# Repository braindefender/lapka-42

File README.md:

[English version of this README](./README_EN.md)

# Лапка 42

Беспроводная эргономичная сплит-клавитура для тех, у кого лапки (:

**Информация:**

|                         |                                 |
| :---------------------- | :------------------------------ |
| **Количество клавиш**   | 42                              |
| **Тип матрицы**         | Диодная                         |
| **Направление диодов**  | Col2Row                         |
| **Совместимые MCU**     | nRF52840 (SuperMini, nice!nano) |
| **Совместимые АКБ**     | 401230                          |
| **Совместимые свитчи**  | Choc v1/v2                      |
| **Свитч-спейсинг**      | Choc (18×17mm)                  |
| **Расположение клавиш** | Splay                           |

**Структура репозитория:**

| Директория | Описание                                              |
| ---------: | :---------------------------------------------------- |
|        3MF | Проект OrcaSlicer (для примера параметров печати)     |
|     Assets | Изображения и фото                                    |
|      Build | Описание [процесса сборки](./Build/BUILD_GUIDE_RU.md) |
|     Fusion | Проект Autodesk Fusion 360                            |
|    Gerbers | Gerber-файлы для производства плат                    |
|      KiCad | Проект KiCad (схема, плата, компоненты)               |
|        STL | 3D-модели частей корпуса                              |

**Части корпуса:**
|   Файл | Описание                                                      |
| -----: | :------------------------------------------------------------ |
| Bottom | Нижняя часть корпуса, имеет вырезы под hotswap-сокеты и диоды |
|  Cover | Крышка для АКБ и кнопки Reset                                 |
|  Frame | Верхняя часть корпуса, для тайп-кластера                      |
|  Thumb | Верхняя часть корпуса, для тамб-кластера                      |

**Разметка пинов:**

> C — колонки, R — строки, нумерация слева направо, сверху вниз

|  Пин  | Левая | Правая |
| :---: | :---: | :----: |
|  C0   |  D4   |  D10   |
|  C1   |  D5   |  D16   |
|  C2   |  D6   |  D14   |
|  C3   |  D7   |  D15   |
|  C4   |  D8   |  D18   |
|  C5   |  D9   |  D19   |
|       |       |
|  R0   |  D2   |  D21   |
|  R1   |  D3   |  D20   |
|  R2   |  D16  |   D8   |
|  R3   |  D10  |   D9   |

## Прошивка

- [`ZMK × Wellum`](https://github.com/braindefender/lapka-zmk-config/tree/lapka-42)
- `RMK × Wellum` — *в разработке*

## История изменений

### v1
- Первичный релиз.

## Фото

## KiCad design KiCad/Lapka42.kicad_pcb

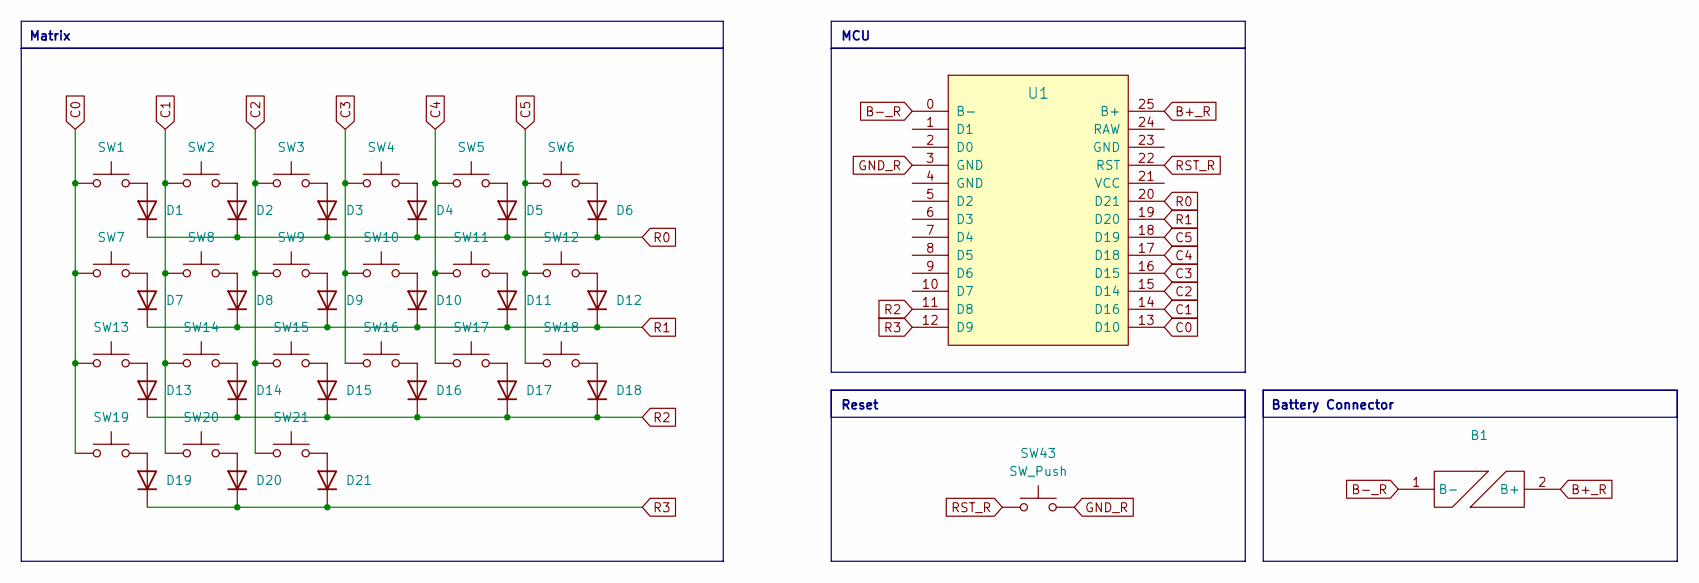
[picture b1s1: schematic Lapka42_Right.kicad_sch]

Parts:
B1: BAT_RECT
D1, D2, D3, D4, D5, D6, D7, D8, D9, D10, D11, D12, D13, D14, D15, D16, D17, D18, D19, D20, D21: D_SOD-323_Increased
SW1, SW2, SW3, SW4, SW5, SW6, SW7, SW8, SW9, SW10, SW11, SW12, SW13, SW14, SW15, SW16, SW17, SW18, SW19, SW20, SW21: SW_Choc_V1V2_HS
SW43: SW_Push; SW_SMD_5x5
U1: U_ProMicro_nRF52840_MidMount

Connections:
B+_R: B1.2 (B+), U1.25 (B+)
B-_R: B1.1 (B-), U1.0 (B-)
C0: SW1.1, SW7.1, SW13.1, SW19.1, U1.13 (D10)
C1: SW2.1, SW8.1, SW14.1, SW20.1, U1.14 (D16)
C2: SW3.1, SW9.1, SW15.1, SW21.1, U1.15 (D14)
C3: SW4.1, SW10.1, SW16.1, U1.16 (D15)
C4: SW5.1, SW11.1, SW17.1, U1.17 (D18)
C5: SW6.1, SW12.1, SW18.1, U1.18 (D19)
GND_R: SW43.2, U1.3 (GND)
unnamed: D1.2 (A), SW1.2
unnamed: D2.2 (A), SW2.2
unnamed: D3.2 (A), SW3.2
unnamed: D4.2 (A), SW4.2
unnamed: D5.2 (A), SW5.2
unnamed: D6.2 (A), SW6.2
unnamed: D7.2 (A), SW7.2
unnamed: D8.2 (A), SW8.2
unnamed: D9.2 (A), SW9.2
unnamed: D10.2 (A), SW10.2
unnamed: D11.2 (A), SW11.2
unnamed: D12.2 (A), SW12.2
unnamed: D13.2 (A), SW13.2
unnamed: D14.2 (A), SW14.2
unnamed: D15.2 (A), SW15.2
unnamed: D16.2 (A), SW16.2
unnamed: D17.2 (A), SW17.2
unnamed: D18.2 (A), SW18.2
unnamed: D19.2 (A), SW19.2
unnamed: D20.2 (A), SW20.2
unnamed: D21.2 (A), SW21.2
R0: D1.1 (K), D2.1 (K), D3.1 (K), D4.1 (K), D5.1 (K), D6.1 (K), U1.20 (D21)
R1: D7.1 (K), D8.1 (K), D9.1 (K), D10.1 (K), D11.1 (K), D12.1 (K), U1.19 (D20)
R2: D13.1 (K), D14.1 (K), D15.1 (K), D16.1 (K), D17.1 (K), D18.1 (K), U1.11 (D8)
R3: D19.1 (K), D20.1 (K), D21.1 (K), U1.12 (D9)
RST_R: SW43.1, U1.22 (RST)

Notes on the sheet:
Battery Connector
MCU
Matrix
Reset

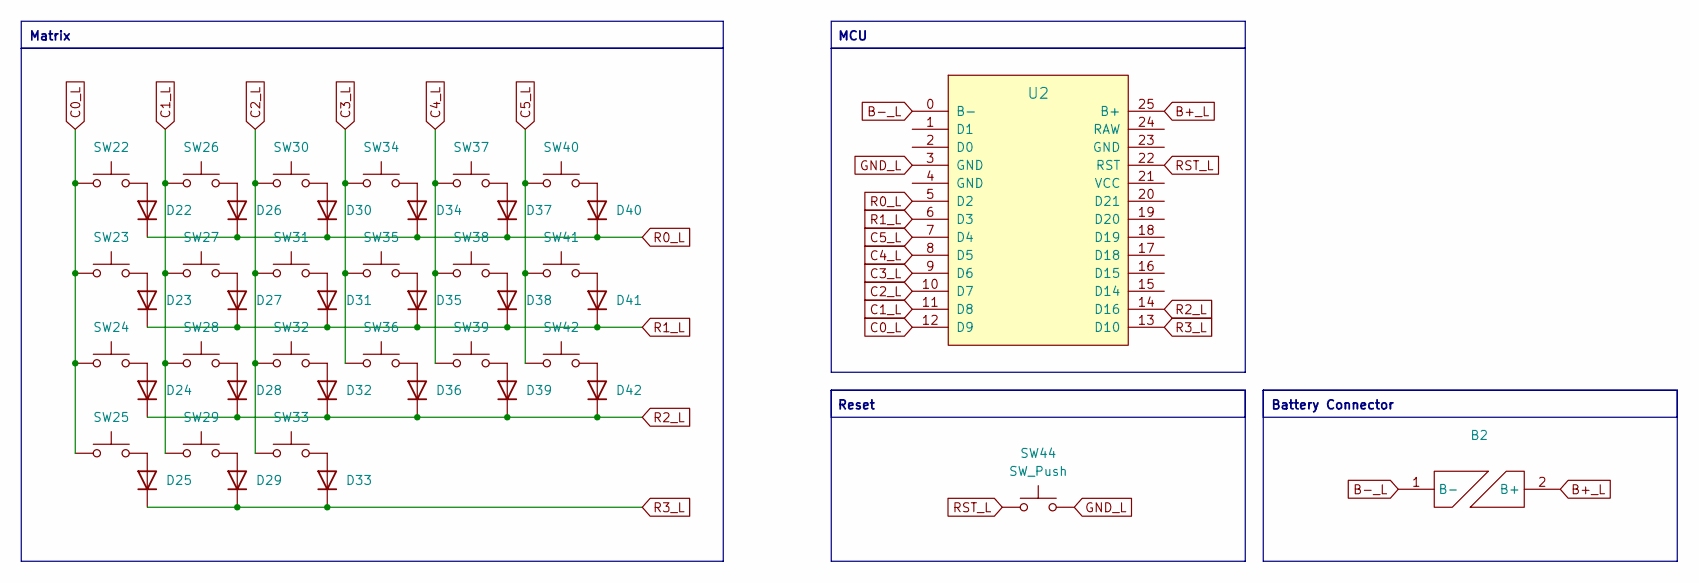
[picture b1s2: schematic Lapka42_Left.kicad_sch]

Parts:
B2: BAT_RECT
D22, D23, D24, D25, D26, D27, D28, D29, D30, D31, D32, D33, D34, D35, D36, D37, D38, D39, D40, D41, D42: D_SOD-323_Increased
SW22, SW23, SW24, SW25, SW26, SW27, SW28, SW29, SW30, SW31, SW32, SW33, SW34, SW35, SW36, SW37, SW38, SW39, SW40, SW41, SW42: SW_Choc_V1V2_HS
SW44: SW_Push; SW_SMD_5x5
U2: U_ProMicro_nRF52840_MidMount

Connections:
B+_L: B2.2 (B+), U2.25 (B+)
B-_L: B2.1 (B-), U2.0 (B-)
C0_L: SW22.1, SW23.1, SW24.1, SW25.1, U2.12 (D9)
C1_L: SW26.1, SW27.1, SW28.1, SW29.1, U2.11 (D8)
C2_L: SW30.1, SW31.1, SW32.1, SW33.1, U2.10 (D7)
C3_L: SW34.1, SW35.1, SW36.1, U2.9 (D6)
C4_L: SW37.1, SW38.1, SW39.1, U2.8 (D5)
C5_L: SW40.1, SW41.1, SW42.1, U2.7 (D4)
GND_L: SW44.2, U2.3 (GND)
unnamed: D22.2 (A), SW22.2
unnamed: D23.2 (A), SW23.2
unnamed: D24.2 (A), SW24.2
unnamed: D25.2 (A), SW25.2
unnamed: D26.2 (A), SW26.2
unnamed: D27.2 (A), SW27.2
unnamed: D28.2 (A), SW28.2
unnamed: D29.2 (A), SW29.2
unnamed: D30.2 (A), SW30.2
unnamed: D31.2 (A), SW31.2
unnamed: D32.2 (A), SW32.2
unnamed: D33.2 (A), SW33.2
unnamed: D34.2 (A), SW34.2
unnamed: D35.2 (A), SW35.2
unnamed: D36.2 (A), SW36.2
unnamed: D37.2 (A), SW37.2
unnamed: D38.2 (A), SW38.2
unnamed: D39.2 (A), SW39.2
unnamed: D40.2 (A), SW40.2
unnamed: D41.2 (A), SW41.2
unnamed: D42.2 (A), SW42.2
R0_L: D22.1 (K), D26.1 (K), D30.1 (K), D34.1 (K), D37.1 (K), D40.1 (K), U2.5 (D2)
R1_L: D23.1 (K), D27.1 (K), D31.1 (K), D35.1 (K), D38.1 (K), D41.1 (K), U2.6 (D3)
R2_L: D24.1 (K), D28.1 (K), D32.1 (K), D36.1 (K), D39.1 (K), D42.1 (K), U2.14 (D16)
R3_L: D25.1 (K), D29.1 (K), D33.1 (K), U2.13 (D10)
RST_L: SW44.1, U2.22 (RST)

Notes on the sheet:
Reset
Matrix
Battery Connector
MCU

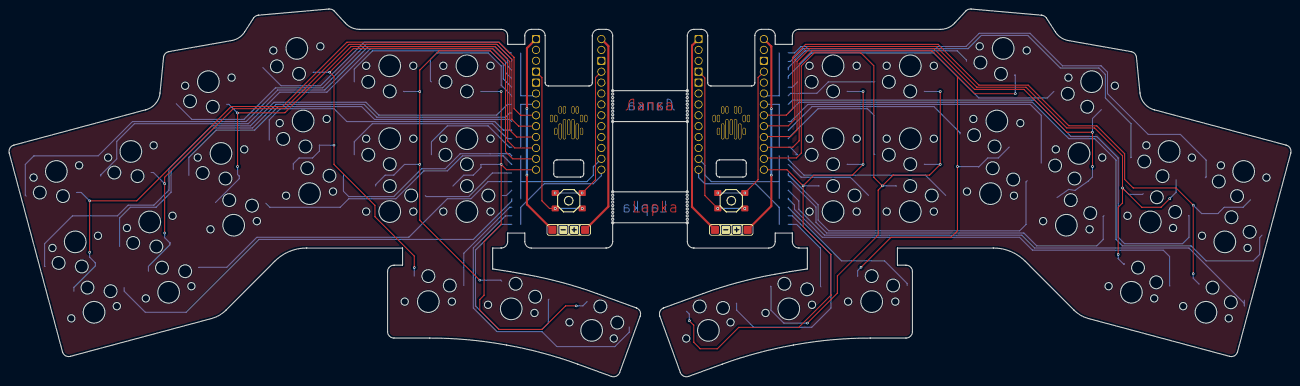
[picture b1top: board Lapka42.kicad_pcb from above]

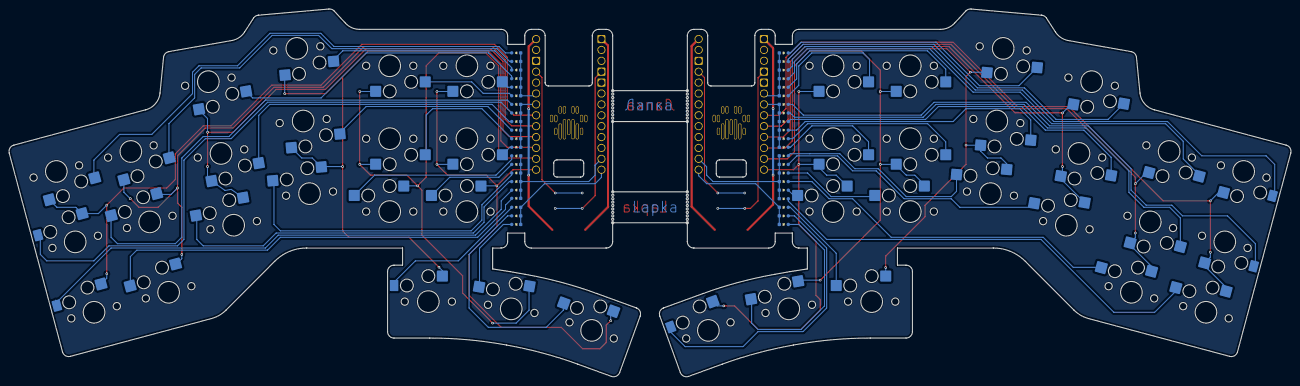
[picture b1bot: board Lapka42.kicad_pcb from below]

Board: 2 copper layers, 299.0 x 85.8 mm, 90 parts (42 on the bottom side), 70 nets.

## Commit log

2026-02-04 feat: add build guide draft
2026-02-06 major: initial release
2026-02-06 fix: remove build
2026-02-06 fix: add build
2026-02-06 fix: build guide
2026-02-07 fix: en readme
2026-02-07 feat: add firmware links
2026-02-07 fix: add choc-v2 THCS keycaps
2026-02-07 fix: add mcu, reset and battery placement photos
2026-02-07 fix: add rubber feet
2026-02-20 fix: update image
